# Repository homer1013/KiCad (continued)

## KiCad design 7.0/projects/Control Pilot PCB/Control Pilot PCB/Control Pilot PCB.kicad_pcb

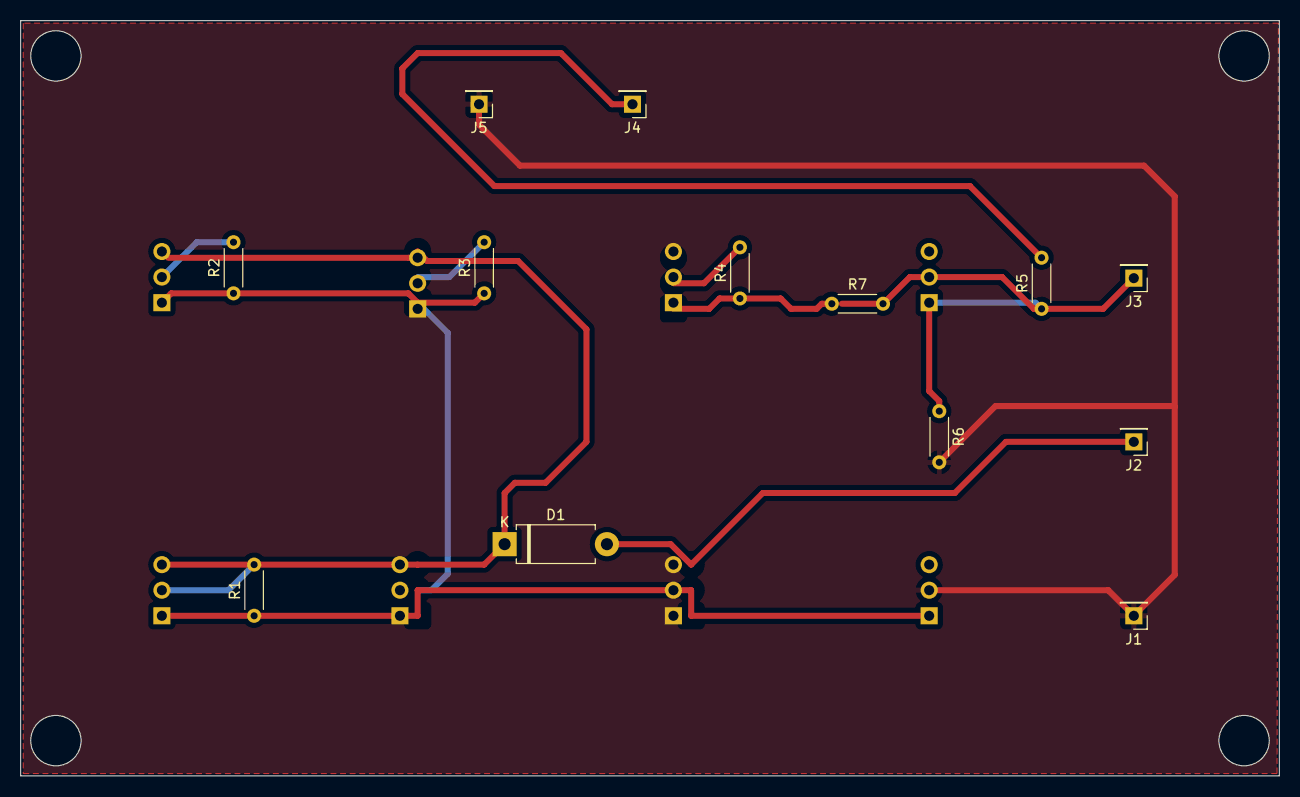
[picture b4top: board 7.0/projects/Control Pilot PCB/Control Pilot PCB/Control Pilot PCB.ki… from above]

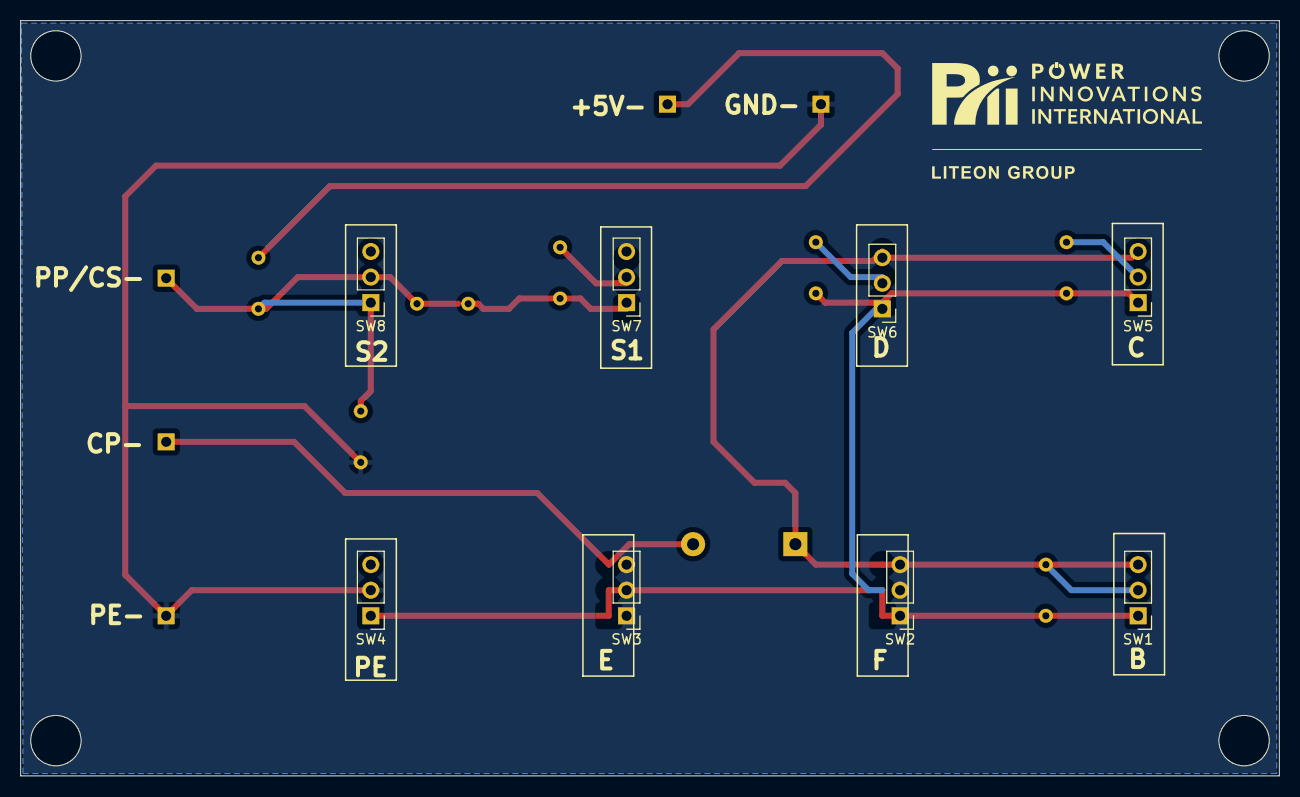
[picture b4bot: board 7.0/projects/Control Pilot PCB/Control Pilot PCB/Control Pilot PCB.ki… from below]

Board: 2 copper layers, 125.0 x 75.0 mm, 21 parts (8 on the bottom side), 11 nets.

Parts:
D1: D; D_DO-15_P10.16mm_Horizontal
J1, J2, J3, J4, J5: Conn_01x01; PinHeader_1x01_P2.54mm_Vertical
R1: 2.74K; R_Axial_DIN0204_L3.6mm_D1.6mm_P5.08mm_Horizontal
R2: 1.3K; R_Axial_DIN0204_L3.6mm_D1.6mm_P5.08mm_Horizontal
R3: 270; R_Axial_DIN0204_L3.6mm_D1.6mm_P5.08mm_Horizontal
R4, R5: 330; R_Axial_DIN0204_L3.6mm_D1.6mm_P5.08mm_Horizontal
R6: 2.7K; R_Axial_DIN0204_L3.6mm_D1.6mm_P5.08mm_Horizontal
R7: 150; R_Axial_DIN0204_L3.6mm_D1.6mm_P5.08mm_Horizontal
SW1, SW2, SW3, SW4, SW5, SW6, SW7, SW8: SW_SPDT; PinHeader_1x03_P2.54mm_Vertical

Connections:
+5V: J4.1, R5.2
Earth_Protective: J1.1, J5.1, R6.2, SW1.2 (B)
unnamed: D1.2 (A), J2.1, SW2.3 (C)
unnamed: D1.1 (K), R1.2, SW3.3 (C), SW4.2 (B), SW4.3 (C), SW7.3 (C), SW8.3 (C)
unnamed: J3.1, R7.2, SW5.2 (B)
unnamed: R1.1, R2.1, R3.1, SW1.1 (A), SW2.1 (A), SW2.2 (B), SW3.1 (A), SW3.2 (B), SW4.1 (A), SW7.1 (A), SW8.1 (A)
unnamed: R5.1, R6.1, SW5.1 (A)
unnamed: R4.1, R7.1, SW6.1 (A)
unnamed: R4.2, SW6.2 (B)
unnamed: R3.2, SW7.2 (B)
unnamed: R2.2, SW8.2 (B)

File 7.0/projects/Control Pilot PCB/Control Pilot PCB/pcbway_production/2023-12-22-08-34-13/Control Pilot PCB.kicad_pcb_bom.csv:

designator,quantity,value,pack,mpn,mount_type
D1,1,D,D_DO-15_P10.16mm_Horizontal,,tht
"J1, J2, J3, J4, J5",5,Conn_01x01,PinHeader_1x01_P2.54mm_Vertical,,tht
R1,1,2.74K,R_Axial_DIN0204_L3.6mm_D1.6mm_P5.08mm_Horizontal,,tht
R2,1,1.3K,R_Axial_DIN0204_L3.6mm_D1.6mm_P5.08mm_Horizontal,,tht
R3,1,270,R_Axial_DIN0204_L3.6mm_D1.6mm_P5.08mm_Horizontal,,tht
"R4, R5",2,330,R_Axial_DIN0204_L3.6mm_D1.6mm_P5.08mm_Horizontal,,tht
R6,1,2.7K,R_Axial_DIN0204_L3.6mm_D1.6mm_P5.08mm_Horizontal,,tht
R7,1,150,R_Axial_DIN0204_L3.6mm_D1.6mm_P5.08mm_Horizontal,,tht
"SW1, SW2, SW3, SW4, SW5, SW6, SW7, SW8",8,SW_SPDT,PinHeader_1x03_P2.54mm_Vertical,,tht

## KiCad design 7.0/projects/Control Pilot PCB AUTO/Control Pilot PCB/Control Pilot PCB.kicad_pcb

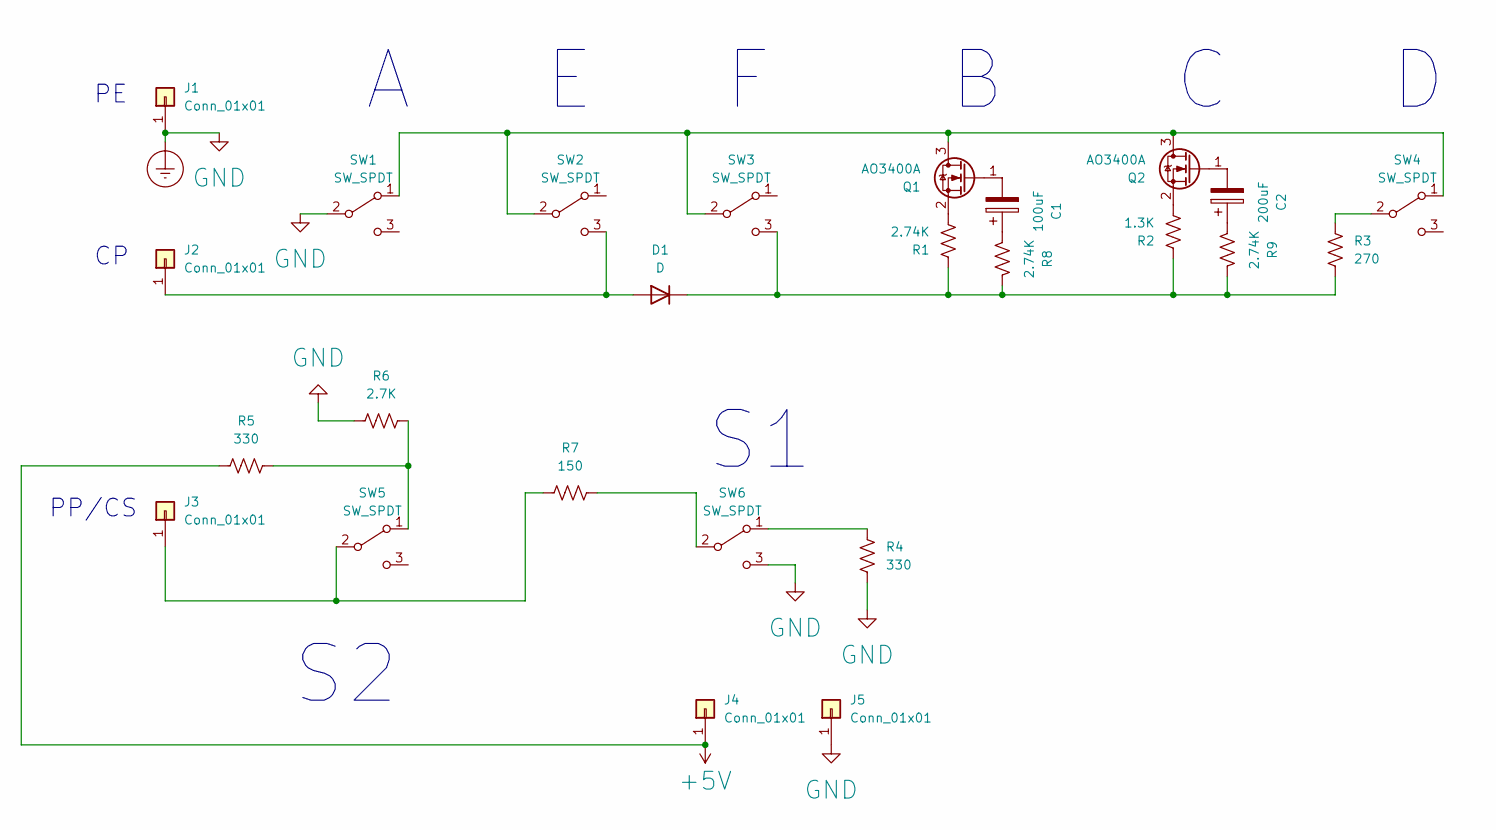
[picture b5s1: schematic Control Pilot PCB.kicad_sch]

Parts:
C1: 100uF; CP_Radial_D6.3mm_P2.50mm
C2: 200uF; CP_Radial_D6.3mm_P2.50mm
D1: D; D_DO-15_P10.16mm_Horizontal
J1, J2, J3, J4, J5: Conn_01x01; PinHeader_1x01_P2.54mm_Vertical
Q1, Q2: AO3400A; SOT-23
R1, R8, R9: 2.74K; R_Axial_DIN0204_L3.6mm_D1.6mm_P5.08mm_Horizontal
R2: 1.3K; R_Axial_DIN0204_L3.6mm_D1.6mm_P5.08mm_Horizontal
R3: 270; R_Axial_DIN0204_L3.6mm_D1.6mm_P5.08mm_Horizontal
R4, R5: 330; R_Axial_DIN0204_L3.6mm_D1.6mm_P5.08mm_Horizontal
R6: 2.7K; R_Axial_DIN0204_L3.6mm_D1.6mm_P5.08mm_Horizontal
R7: 150; R_Axial_DIN0204_L3.6mm_D1.6mm_P5.08mm_Horizontal
SW1, SW2, SW3, SW4, SW5, SW6: SW_SPDT; PinHeader_1x03_P2.54mm_Vertical

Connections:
+5V: J4.1, R5.2
Earth_Protective: J1.1, J5.1, R4.2, R6.2, SW1.2 (B), SW6.3 (C)
unnamed: C1.1, R8.2
unnamed: C2.1, R9.2
unnamed: D1.2 (A), J2.1, SW2.3 (C)
unnamed: D1.1 (K), R1.1, R2.1, R3.2, R8.1, R9.1, SW3.3 (C)
unnamed: J3.1, R7.2, SW5.2 (B)
unnamed: Q1.3 (D), Q2.3 (D), SW1.1 (A), SW2.2 (B), SW3.2 (B), SW4.1 (A)
unnamed: C1.2, Q1.1 (G)
unnamed: Q1.2 (S), R1.2
unnamed: C2.2, Q2.1 (G)
unnamed: Q2.2 (S), R2.2
unnamed: R3.1, SW4.2 (B)
unnamed: R5.1, R6.1, SW5.1 (A)
unnamed: R4.1, SW6.1 (A)
unnamed: R7.1, SW6.2 (B)

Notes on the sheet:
PP/CS

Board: 2 copper layers, 25 parts (0 on the bottom side), 16 nets, no tracks yet.

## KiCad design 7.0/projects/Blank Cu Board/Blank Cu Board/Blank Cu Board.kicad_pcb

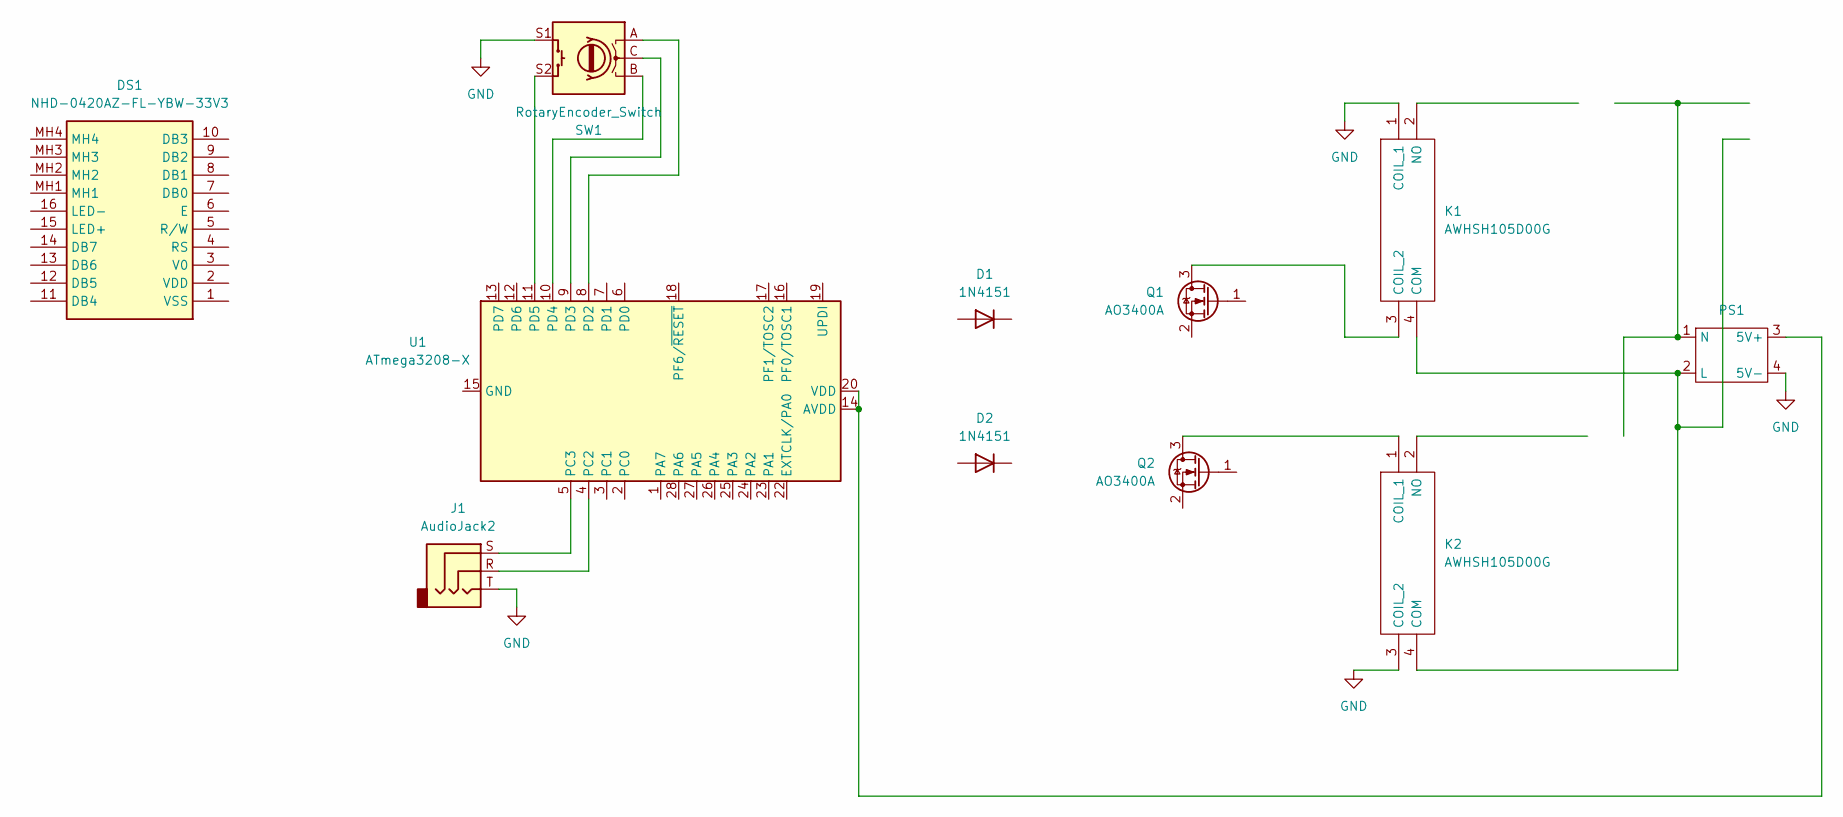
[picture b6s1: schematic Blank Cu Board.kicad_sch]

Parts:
D1, D2: 1N4151; D_DO-35_SOD27_P7.62mm_Horizontal
DS1: NHD-0420AZ-FL-YBW-33V3; NHD0420AZFLYBW33V3_MODIFIED; Mouser Part Number 763-0420AZFLYBW33V3
J1: AudioJack2; Jack_3.5mm_CUI_SJ1-3523N_Horizontal
K1, K2: AWHSH105D00G; Mouser Part Number 523-AWHSH105D00G
PS1: SM-PLG06A
Q1, Q2: AO3400A; SOT-23
SW1: RotaryEncoder_Switch; RotaryEncoder_Alps_EC11E-Switch_Vertical_H20mm
U1: ATmega3208-X; SSOP-28_5.3x10.2mm_P0.65mm

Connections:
GND: J1.T, K1.1 (COIL_1), K2.3 (COIL_2), PS1.4 (5V-), SW1.S1
unnamed: K1.3 (COIL_2), Q1.3 (D)
unnamed: K1.4 (COM), K2.4 (COM), PS1.2 (L)
unnamed: K2.1 (COIL_1), Q2.3 (D)
unnamed: PS1.3 (5V+), U1.14 (AVDD), U1.20 (VDD)
unnamed: U1.15 (GND), U1.21 (GND)
unnamed: J1.R, U1.4 (PC2)
unnamed: J1.S, U1.5 (PC3)
unnamed: SW1.A, U1.8 (PD2)
unnamed: SW1.C, U1.9 (PD3)
unnamed: SW1.B, U1.10 (PD4)
unnamed: SW1.S2, U1.11 (PD5)

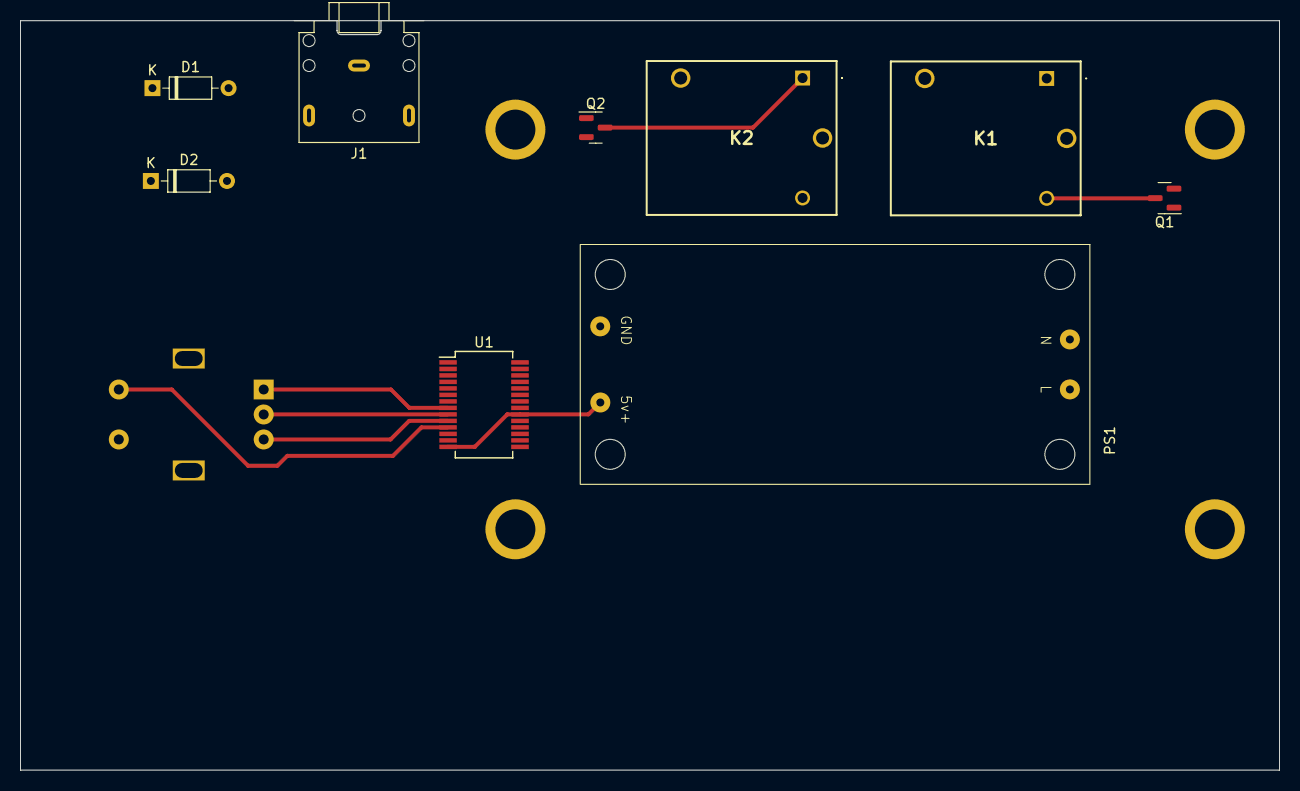
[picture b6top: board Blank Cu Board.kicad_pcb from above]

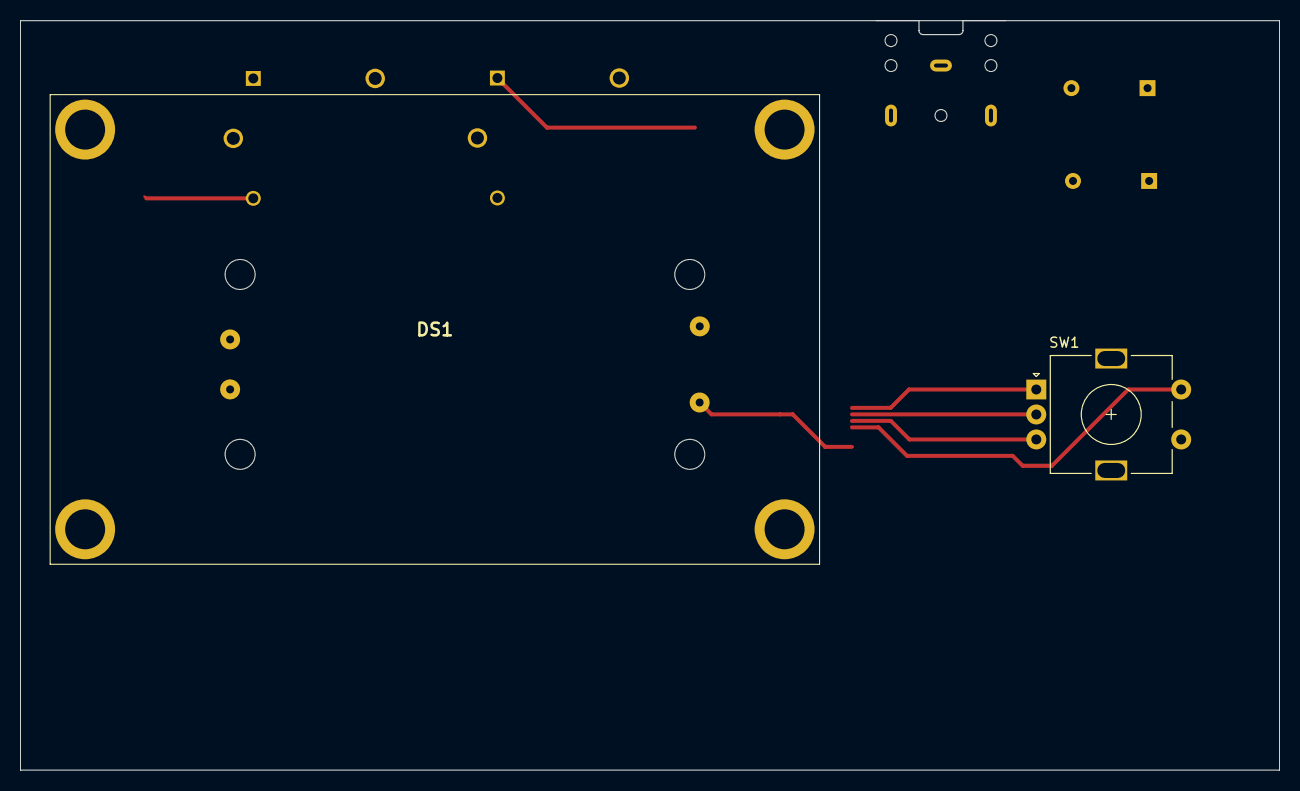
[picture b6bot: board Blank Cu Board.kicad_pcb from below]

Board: 2 copper layers, 126.0 x 75.0 mm, 11 parts (2 on the bottom side), 12 nets.

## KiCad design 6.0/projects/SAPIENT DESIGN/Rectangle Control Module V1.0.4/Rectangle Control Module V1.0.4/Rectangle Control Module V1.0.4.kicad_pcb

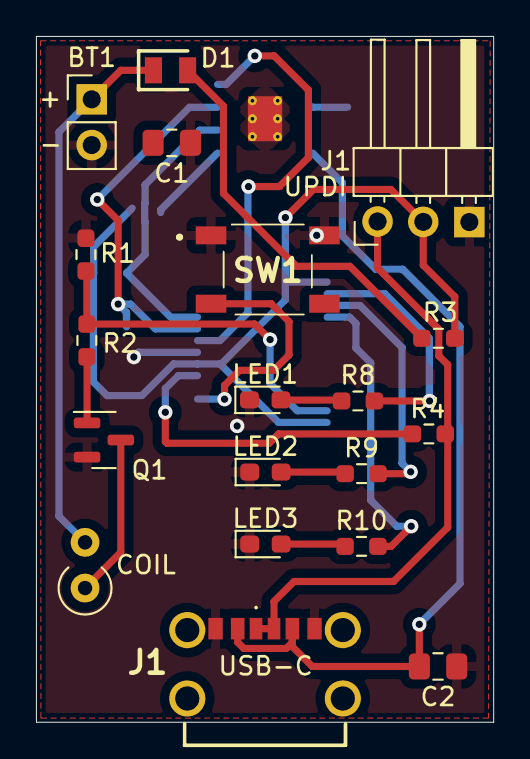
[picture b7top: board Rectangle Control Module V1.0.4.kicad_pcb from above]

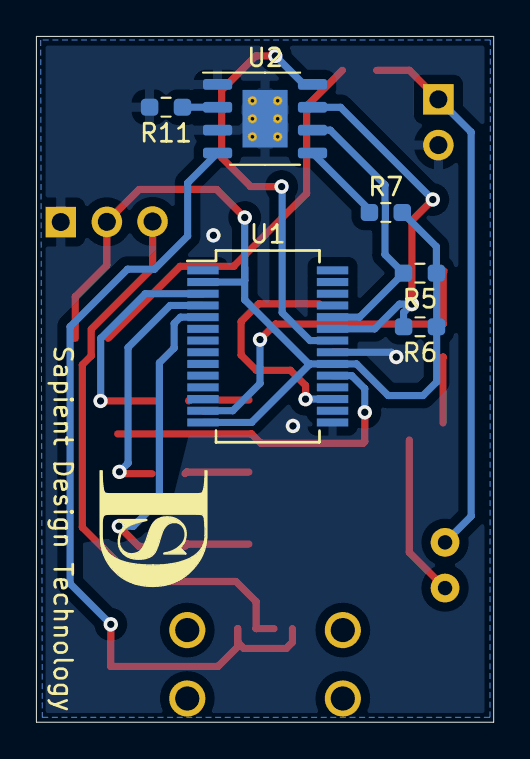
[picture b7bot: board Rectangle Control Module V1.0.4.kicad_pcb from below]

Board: 2 copper layers, 25.4 x 38.1 mm, 25 parts (6 on the bottom side), 22 nets.

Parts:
BT1: Battery_Cell; PinHeader_1x02_P2.54mm_Vertical
C1, C2: 10uF; C_0805_2012Metric_Pad1.18x1.45mm_HandSolder
COIL: 2 Ohm; L_Axial_L6.6mm_D2.7mm_P2.54mm_Vertical_Vishay_IM-2
D1: D_Schottky; DIOC2013X100N
J1: USB4125GFA0190
J1#2: Conn_01x03_Male; PinHeader_1x03_P2.54mm_Horizontal
LED1, LED2, LED3: LED; LED_0603_1608Metric_Pad1.05x0.95mm_HandSolder
Q1: AO3400A; SOT-23
R1, R7: 100K; R_0603_1608Metric_Pad0.98x0.95mm_HandSolder
R2, R4, R5, R6: 4.7K; R_0603_1608Metric_Pad0.98x0.95mm_HandSolder
R3: 100; R_0603_1608Metric_Pad0.98x0.95mm_HandSolder
R8, R9, R10: 1K; R_0603_1608Metric_Pad0.98x0.95mm_HandSolder
R11: 2.8K; R_0603_1608Metric_Pad0.98x0.95mm_HandSolder
SW1: btn; 814375651
U1: ATmega3208-X; SSOP-28_5.3x10.2mm_P0.65mm
U2: TP4056; SOIC-8-1EP_3.9x4.9mm_P1.27mm_EP2.514x3.2mm_ThermalVias

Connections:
GND: BT1.2 (-), C1.1, C2.1, J1.A12 (GND_1), J1.B12 (GND_2), J1#2.1, LED1.1 (K), LED2.1 (K), LED3.1 (K), Q1.2, R1.1, R11.2, SW1.1 (COM_1), SW1.2 (COM_2), U1.15 (GND), U1.21 (GND), U2.1 (TEMP1), U2.3 (GND_3), U2.9 (EP)
unnamed: D1.2, R3.1
unnamed: C2.2, J1.A9 (VBUS_1), J1.B9 (VBUS_2), U2.4 (VCC4)
unnamed: LED1.2 (A), R8.1
unnamed: LED2.2 (A), R9.1
unnamed: LED3.2 (A), R10.1
unnamed: J1#2.2, R3.2, R5.1, R6.1, R7.2, U1.2 (PC0), U1.14 (AVDD), U1.20 (VDD)
unnamed: J1.A5 (CC1), J1.B5 (CC2), J1#2.3, R4.2
unnamed: COIL.1, Q1.3
unnamed: BT1.1 (+), COIL.2, D1.1
unnamed: Q1.1, R2.1
unnamed: R1.2, R2.2, U1.13 (PD7)
unnamed: R4.1, U1.19 (UPDI)
unnamed: R5.2, U1.24 (PA2), U2.6 (~STDBY)
unnamed: R6.2, U1.23 (PA1), U2.7 (~CHRG)
unnamed: R7.1, U2.5 (BAT)
unnamed: R8.2, U1.3 (PC1)
unnamed: R9.2, U1.4 (PC2)
unnamed: R10.2, U1.5 (PC3)
unnamed: R11.1, U2.2 (PROG2)
unnamed: SW1.3 (NO_1), U1.17 (PF1/TOSC2)
unnamed: U1.22 (EXTCLK/PA0), U2.8 (CE)

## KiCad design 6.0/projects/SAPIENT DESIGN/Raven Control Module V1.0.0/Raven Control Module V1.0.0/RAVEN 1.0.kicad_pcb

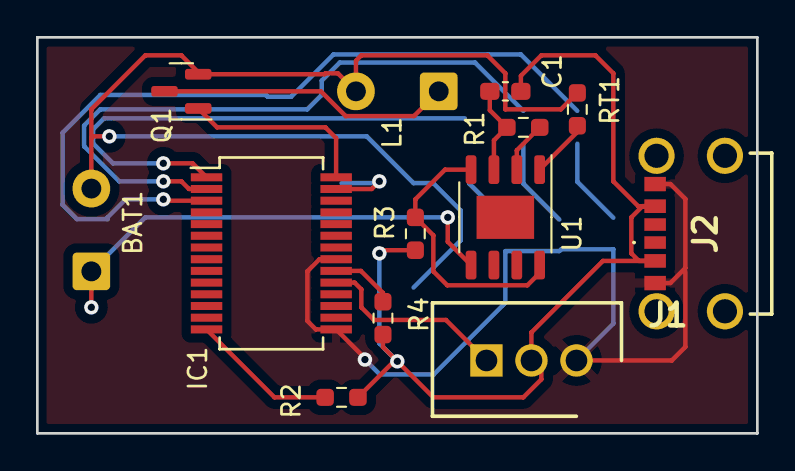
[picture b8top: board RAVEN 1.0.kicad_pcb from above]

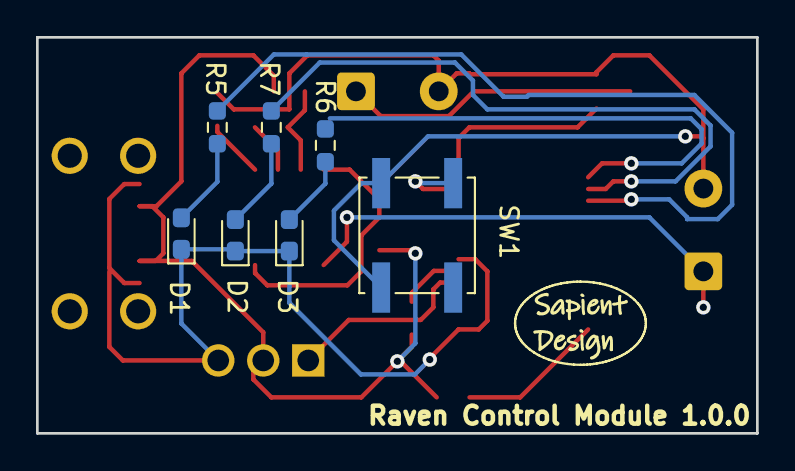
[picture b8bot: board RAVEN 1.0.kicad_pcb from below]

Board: 2 copper layers, 40.0 x 22.0 mm, 20 parts (7 on the bottom side), 20 nets.

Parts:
BAT1: Battery_Cell; SolderWire-0.5sqmm_1x02_P4.6mm_D0.9mm_OD2.1mm
C1: 10uf; C_0603_1608Metric_Pad1.08x0.95mm_HandSolder
D1, D2, D3: LED; LED_0603_1608Metric_Pad1.05x0.95mm_HandSolder
IC1: ATMEGA3208-XFR; SSOP-28_5.3x10.2mm_P0.65mm
J1: UPDI HEADER; SHDR3W69P0X250_1X3_1000X600X790P
J2: USB_C_Receptacle_USB2.0; USB4125GFA0190
L1: L; SolderWire-0.5sqmm_1x02_P4.6mm_D0.9mm_OD2.1mm
Q1: SI3402-TP; SOT-23
R1: 1k; R_0603_1608Metric_Pad0.98x0.95mm_HandSolder
R2, R3, R4: .4; R_0603_1608Metric_Pad0.98x0.95mm_HandSolder
R5, R6, R7: R; R_0603_1608Metric_Pad0.98x0.95mm_HandSolder
RT1: NTCG163JF103FT1; R_0603_1608Metric_Pad0.98x0.95mm_HandSolder
SW1: TS02-66-43-BK-260-LCR-D; SW_Push_1P1T_NO_CK_KSC7xxJ
U1: TP4056; HTSOP-8-1EP_3.9x4.9mm_P1.27mm_EP2.4x3.2mm

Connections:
unnamed: BAT1.1 (+), U1.5 (BAT)
unnamed: BAT1.2 (-), L1.2, Q1.2, RT1.2, SW1.2 (NO)
unnamed: C1.1, R1.2, U1.3 (GND_3)
unnamed: C1.2, J1.2, J2.A9 (VBUS), J2.B9 (VBUS), R2.2, R3.2, R4.1
unnamed: D1.1 (K), D2.1 (K), D3.1 (K), IC1.15 (GND_1), IC1.21 (GND_2), J1.3, J2.A12 (GND), J2.B12 (GND), J2.MH2
unnamed: D1.2 (A), R5.1
unnamed: D2.2 (A), R7.1
unnamed: D3.2 (A), R6.1
unnamed: IC1.1 (PA7), R6.2
unnamed: IC1.2 (PC0), R7.2
unnamed: IC1.3 (PC1), R5.2
unnamed: IC1.14 (AVDD), R2.1
unnamed: IC1.19 (UPDI), J1.1
unnamed: IC1.20 (VDD), R4.2
unnamed: IC1.27 (PA5), SW1.1 (NO)
unnamed: IC1.28 (PA6), Q1.1
unnamed: L1.1, Q1.3
unnamed: R1.1, U1.2 (PROG2)
unnamed: R3.1, U1.4 (VCC4), U1.8 (CE)
unnamed: RT1.1, U1.1 (TEMP1)

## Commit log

2023-10-30 Adding KiCad stuff
2024-01-25 Mass Update
2024-05-14 Minor Updates
2024-06-18 stuff
2024-07-09 fyukgkjl
2024-07-25 upppp
